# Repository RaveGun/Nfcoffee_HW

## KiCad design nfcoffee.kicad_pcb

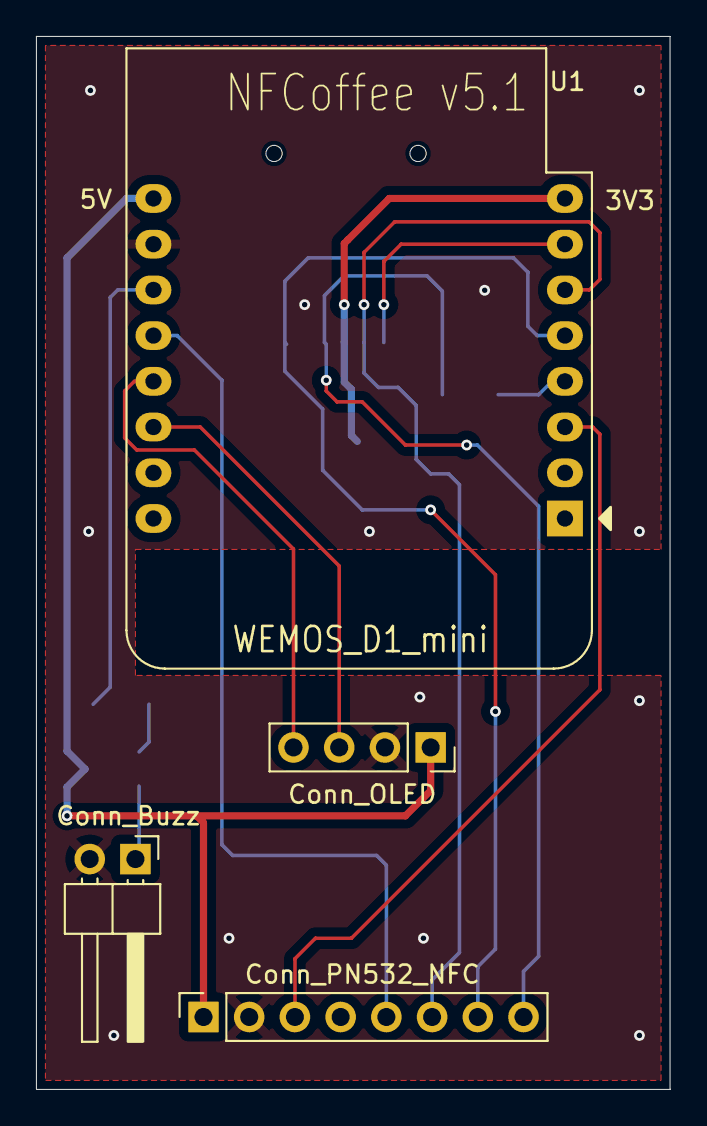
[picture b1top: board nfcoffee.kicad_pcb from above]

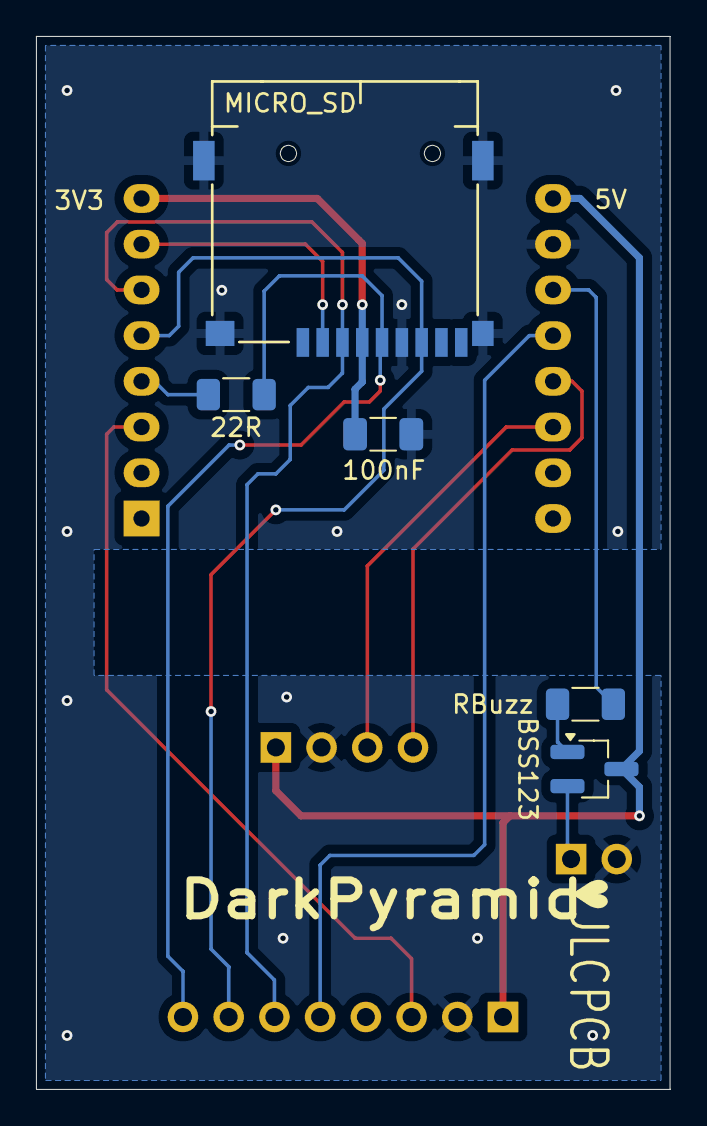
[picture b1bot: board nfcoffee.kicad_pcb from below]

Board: 2 copper layers, 35.2 x 58.5 mm, 9 parts (5 on the bottom side), 15 nets.

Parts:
C1: 100nF; C_1206_3216Metric_Pad1.33x1.80mm_HandSolder
J1: Conn_Buzz; PinHeader_1x02_P2.54mm_Horizontal
J5: Conn_OLED; PinSocket_1x04_P2.54mm_Vertical
J6: Conn_PN532_NFC; PinSocket_1x08_P2.54mm_Vertical
MICRO_SD: MICRO_SD(TFC-9P-1.xH(ATFFS150A01BR016)); J_SD_Card-micro_socket_A
Q1: BSS123; SOT-23_Handsoldering
RBuzz: R; R_1206_3216Metric_Pad1.30x1.75mm_HandSolder
RSCK1: 22R; R_1206_3216Metric_Pad1.30x1.75mm_HandSolder
U1: WEMOS_D1_mini; WEMOS_D1_mini_light

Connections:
3V3: C1.1, MICRO_SD.4 (VDD), U1.8 (3V3)
5V: J5.1, J6.1, Q1.3 (D), U1.9 (5V)
GND: C1.2, J1.2, J5.2, J6.2, MICRO_SD.6 (GND), MICRO_SD.SH (Card_Housing), U1.10 (GND)
GPIO0: J6.5, U1.12 (D3)
GPIO2: RBuzz.1, U1.11 (D4)
GPIO4: J5.4, U1.13 (SDA/D2)
GPIO5: J5.3, U1.14 (SCL/D1)
GPIO12: J6.7, MICRO_SD.7 (DAT0/DO), U1.5 (MISO/D6)
GPIO13: J6.6, MICRO_SD.3 (CMD/DI), U1.6 (MOSI/D7)
GPIO14: J6.8, MICRO_SD.5 (CLK/SCLK), RSCK1.2
GPIO15: MICRO_SD.2 (CD/DAT3/CS), U1.7 (CS/D8)
GPIO16: J6.3, U1.3 (D0)
unnamed: J1.1, Q1.2 (S)
unnamed: Q1.1 (G), RBuzz.2
SCK: RSCK1.1, U1.4 (SCK/D5)

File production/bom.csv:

Designator,Footprint,Quantity,Value,LCSC Part #
C1,1206,1,100nF,
J1,PinHeader_1x02_P2.54mm_Horizontal,1,Conn_Buzz,
J5,PinSocket_1x04_P2.54mm_Vertical,1,Conn_OLED,
J6,PinSocket_1x08_P2.54mm_Vertical,1,Conn_PN532_NFC,
MICRO_SD,J_SD_Card-micro_socket_A,1,MICRO_SD(TFC-9P-1.xH(ATFFS150A01BR016)),
Q1,SOT-23_Handsoldering,1,BSS123,
RBUZZ,1206,1,R,
RSCK1,1206,1,22R,
U1,WEMOS_D1_mini_light,1,WEMOS_D1_mini,

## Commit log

2025-03-10 v4_fixed release boards are done and working
2025-03-11 added SD card to PCB on the wrong layer
2025-03-13 Removed SD Shield and replaced with a SD Card Connector directly. Removed current limiting resistors.
2025-03-14 Final changes on text after SD Card layout validation. Sent to JLC as v5.
2025-03-27 Version 5.1 - fixed the connection for the SD card chipselect, moved to GPIO15; - added 22 ohm resistor at the start of SPI CLK line; -removed the voltage divisor for PN532 CIPO because the SPI works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
